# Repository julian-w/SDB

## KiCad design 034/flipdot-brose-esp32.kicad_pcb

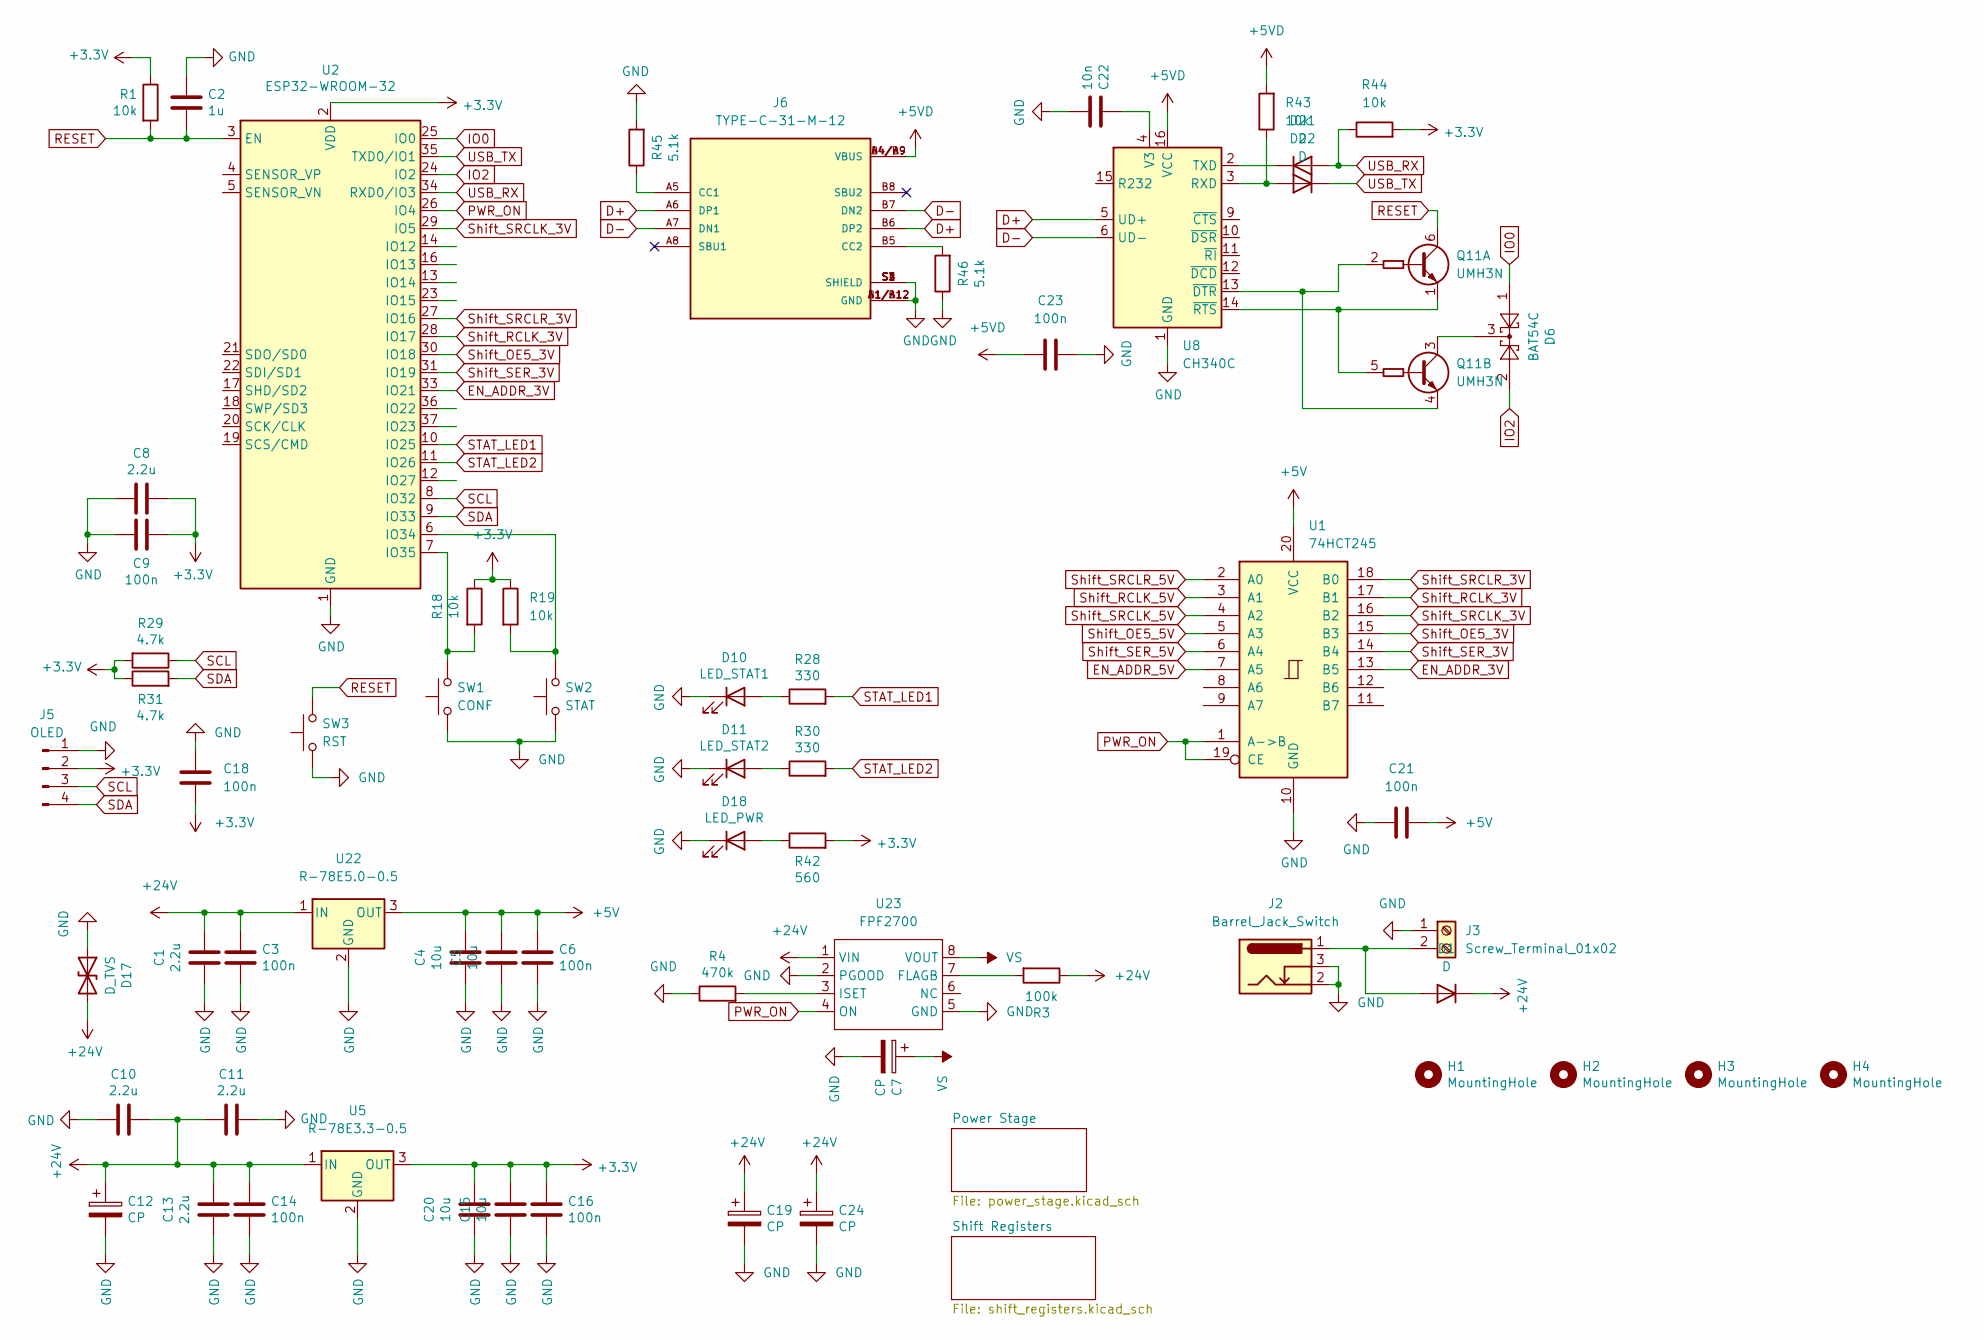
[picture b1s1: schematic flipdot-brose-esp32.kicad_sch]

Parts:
C1, C10, C11, C13: 2.2u; C_0805_2012Metric; LCSC C49217
C2: 1u; C_0603_1608Metric; LCSC C15849
C3, C14: 100n; C_0805_2012Metric; LCSC C49678
C4, C5, C15, C20: 10u; C_0805_2012Metric; LCSC C440198
C6, C9, C16, C18, C21, C23: 100n; C_0603_1608Metric; LCSC C14663
C7, C12, C19, C24: CP; C_Elec_6.3x7.7; LCSC C176683
C8: 2.2u; C_0603_1608Metric; LCSC C23630
C22: 10n; C_0603_1608Metric; LCSC C57112
D1: D; D_SMA; LCSC C14996
D6: BAT54C; SOT-23; LCSC C37704
D10: LED_STAT1; LED_0603_1608Metric; LCSC C72041
D11: LED_STAT2; LED_0603_1608Metric; LCSC C2290
D17: D_TVS; D_SMA; LCSC C152118
D18: LED_PWR; LED_0603_1608Metric; LCSC C2286
D21, D22: D; D_SOD-123; LCSC C81598
H1, H2, H3, H4: MountingHole; MountingHole_2.7mm_M2.5
J2: Barrel_Jack_Switch; BarrelJack_Horizontal
J3: Screw_Terminal_01x02; PhoenixContact_MCV_1,5_2-G-3.5_1x02_P3.50mm_Vertical
J5: OLED; SSD1306-0.91-OLED-4pin-128x32
J6: TYPE-C-31-M-12; HRO_TYPE-C-31-M-12; PARTREV 2020.12.08; LCSC C165948
Q11: UMH3N; SOT-363_SC-70-6; LCSC C62892
R1, R18, R19, R43, R44: 10k; R_0603_1608Metric; LCSC C25804
R3: 100k; R_0603_1608Metric; LCSC C25803
R4: 470k; R_0603_1608Metric; LCSC C23178
R28, R30: 330; R_0603_1608Metric; LCSC C23138
R29, R31: 4.7k; R_0603_1608Metric; LCSC C23162
R42: 560; R_0603_1608Metric; LCSC C23204
R45, R46: 5.1k; R_0603_1608Metric; LCSC C23186
SW1: CONF; SW_Push_1P1T_NO_6x6mm_H9.5mm; LCSC C2837532
SW2: STAT; SW_Push_1P1T_NO_6x6mm_H9.5mm; LCSC C2837532
SW3: RST; SW_Push_1P1T_NO_6x6mm_H9.5mm; LCSC C2837532
U1: 74HCT245; TSSOP-20_4.4x6.5mm_P0.65mm; LCSC C5980
U2: ESP32-WROOM-32; ESP32-WROOM-32U; LCSC C529579
U5: R-78E3.3-0.5; Converter_DCDC_RECOM_R-78E-0.5_THT
U8: CH340C; SOIC-16_3.9x9.9mm_P1.27mm; LCSC C84681
U22: R-78E5.0-0.5; Converter_DCDC_RECOM_R-78E-0.5_THT
U23: FPF2700; SOP-8_3.9x4.9mm_P1.27mm

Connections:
+3V3: C8.1, C9.1, C15.1, C16.1, C18.2, C20.1, J5.2, R1.1, R18.1, R19.1, R29.2, R31.1, R42.2, R44.2, U2.2 (VDD), U5.3 (OUT)
+5V: C4.1, C5.1, C6.1, C21.2, U1.20 (VCC), U22.3 (OUT); also elsewhere on the board
+5VD: C23.2, J6.A4/B9 (VBUS), J6.B4/A9 (VBUS), R43.2, U8.16 (VCC)
+24V: C1.1, C3.1, C10.1, C11.1, C12.1, C13.1, C14.1, C19.1, C24.1, D1.1 (K), D17.2 (A2), R3.1, U5.1 (IN), U22.1 (IN), U23.1 (VIN); also elsewhere on the board
D+: J6.A6 (DP1), J6.B6 (DP2), U8.5 (UD+)
D-: J6.A7 (DN1), J6.B7 (DN2), U8.6 (UD-)
EN_ADDR_3V: U1.13 (B5), U2.33 (IO21)
EN_ADDR_5V: U1.7 (A5); also elsewhere on the board
GND: C1.2, C2.2, C3.2, C4.2, C5.2, C6.2, C7.2, C8.2, C9.2, C10.2, C11.2, C12.2, C13.2, C14.2, C15.2, C16.2, C18.1, C19.2, C20.2, C21.1, C22.2, C23.1, C24.2, D10.1 (K), D11.1 (K), D17.1 (A1), D18.1 (K), J2.2, J2.3, J3.1, J5.1, J6.A1/B12 (GND), J6.B1/A12 (GND), J6.S1 (SHIELD), J6.S2 (SHIELD), J6.S3 (SHIELD), J6.S4 (SHIELD), R4.1, R45.2, R46.1, SW1.1, SW2.1, SW3.1, U1.10 (GND), U2.1 (GND), U2.15 (GND), U2.38 (GND), U2.39 (GND), U5.2 (GND), U8.1 (GND), U22.2 (GND), U23.2 (PGOOD), U23.5 (GND); also elsewhere on the board
IO0: D6.1, U2.25 (IO0)
IO2: D6.2, U2.24 (IO2)
unnamed: C22.1, U8.4 (V3)
unnamed: D1.2 (A), J2.1, J3.2
unnamed: D6.3, Q11.3 (C2)
unnamed: D10.2 (A), R28.1
unnamed: D11.2 (A), R30.1
unnamed: D18.2 (A), R42.1
unnamed: D21.1 (K), U8.2 (TXD)
unnamed: D22.2 (A), R43.1, U8.3 (RXD)
unnamed: J6.A5 (CC1), R45.1
unnamed: J6.B5 (CC2), R46.2
unnamed: Q11.1 (E1), Q11.5 (B2), U8.14 (~RTS)
unnamed: Q11.2 (B1), Q11.4 (E2), U8.13 (~DTR)
unnamed: R3.2, U23.7 (FLAGB)
unnamed: R4.2, U23.3 (ISET)
unnamed: R18.2, SW1.2, U2.7 (IO35)
unnamed: R19.2, SW2.2, U2.6 (IO34)
PWR_ON: U1.1 (A->B), U1.19 (CE), U2.26 (IO4), U23.4 (ON)
RESET: C2.1, Q11.6 (C1), R1.2, SW3.2, U2.3 (EN)
SCL: J5.3, R29.1, U2.8 (IO32)
SDA: J5.4, R31.2, U2.9 (IO33)
STAT_LED1: R28.2, U2.10 (IO25)
STAT_LED2: R30.2, U2.11 (IO26)
Shift_OE5_3V: U1.15 (B3), U2.30 (IO18)
Shift_OE5_5V: U1.5 (A3); also elsewhere on the board
Shift_RCLK_3V: U1.17 (B1), U2.28 (IO17)
Shift_RCLK_5V: U1.3 (A1); also elsewhere on the board
Shift_SER_3V: U1.14 (B4), U2.31 (IO19)
Shift_SER_5V: U1.6 (A4); also elsewhere on the board
Shift_SRCLK_3V: U1.16 (B2), U2.29 (IO5)
Shift_SRCLK_5V: U1.4 (A2); also elsewhere on the board
Shift_SRCLR_3V: U1.18 (B0), U2.27 (IO16)
Shift_SRCLR_5V: U1.2 (A0); also elsewhere on the board
USB_RX: D21.2 (A), R44.1, U2.34 (RXD0/IO3)
USB_TX: D22.1 (K), U2.35 (TXD0/IO1)
VS: C7.1, U23.8 (VOUT); also elsewhere on the board

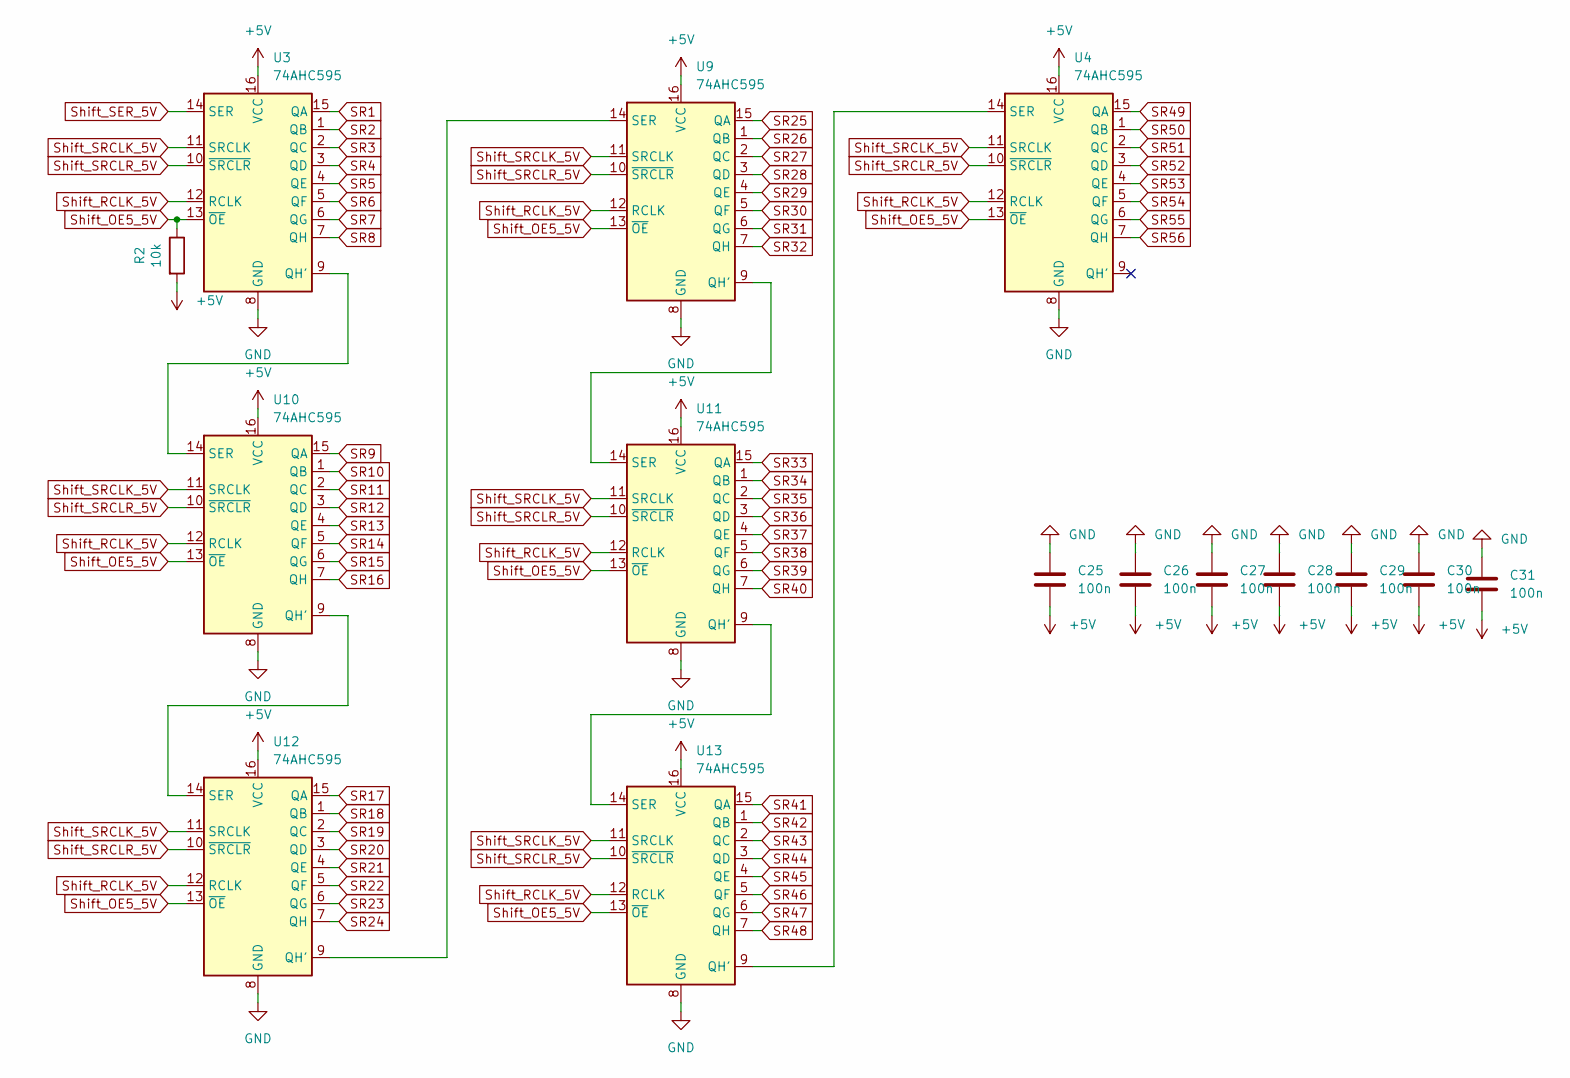
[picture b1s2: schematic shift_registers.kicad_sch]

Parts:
C25, C26, C27, C28, C29, C30, C31: 100n; C_0603_1608Metric; LCSC C14663
R2: 10k; R_0603_1608Metric; LCSC C25804
U3, U4, U9, U10, U11, U12, U13: 74AHC595; TSSOP-16_4.4x5mm_P0.65mm; LCSC C271269

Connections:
+5V: C25.2, C26.2, C27.2, C28.2, C29.2, C30.2, C31.2, R2.2, U3.16 (VCC), U4.16 (VCC), U9.16 (VCC), U10.16 (VCC), U11.16 (VCC), U12.16 (VCC), U13.16 (VCC); also elsewhere on the board
GND: C25.1, C26.1, C27.1, C28.1, C29.1, C30.1, C31.1, U3.8 (GND), U4.8 (GND), U9.8 (GND), U10.8 (GND), U11.8 (GND), U12.8 (GND), U13.8 (GND); also elsewhere on the board
unnamed: U10.9 (QH'), U12.14 (SER)
unnamed: U3.9 (QH'), U10.14 (SER)
unnamed: U11.9 (QH'), U13.14 (SER)
unnamed: U9.9 (QH'), U11.14 (SER)
unnamed: U9.14 (SER), U12.9 (QH')
unnamed: U4.14 (SER), U13.9 (QH')
SR1: U3.15 (QA); also elsewhere on the board
SR2: U3.1 (QB); also elsewhere on the board
SR3: U3.2 (QC); also elsewhere on the board
SR4: U3.3 (QD); also elsewhere on the board
SR5: U3.4 (QE); also elsewhere on the board
SR6: U3.5 (QF); also elsewhere on the board
SR7: U3.6 (QG); also elsewhere on the board
SR8: U3.7 (QH); also elsewhere on the board
SR9: U10.15 (QA); also elsewhere on the board
SR10: U10.1 (QB); also elsewhere on the board
SR11: U10.2 (QC); also elsewhere on the board
SR12: U10.3 (QD); also elsewhere on the board
SR13: U10.4 (QE); also elsewhere on the board
SR14: U10.5 (QF); also elsewhere on the board
SR15: U10.6 (QG); also elsewhere on the board
SR16: U10.7 (QH); also elsewhere on the board
SR17: U12.15 (QA); also elsewhere on the board
SR18: U12.1 (QB); also elsewhere on the board
SR19: U12.2 (QC); also elsewhere on the board
SR20: U12.3 (QD); also elsewhere on the board
SR21: U12.4 (QE); also elsewhere on the board
SR22: U12.5 (QF); also elsewhere on the board
SR23: U12.6 (QG); also elsewhere on the board
SR24: U12.7 (QH); also elsewhere on the board
SR25: U9.15 (QA); also elsewhere on the board
SR26: U9.1 (QB); also elsewhere on the board
SR27: U9.2 (QC); also elsewhere on the board
SR28: U9.3 (QD); also elsewhere on the board
SR29: U9.4 (QE); also elsewhere on the board
SR30: U9.5 (QF); also elsewhere on the board
SR31: U9.6 (QG); also elsewhere on the board
SR32: U9.7 (QH); also elsewhere on the board
SR33: U11.15 (QA); also elsewhere on the board
SR34: U11.1 (QB); also elsewhere on the board
SR35: U11.2 (QC); also elsewhere on the board
SR36: U11.3 (QD); also elsewhere on the board
SR37: U11.4 (QE); also elsewhere on the board
SR38: U11.5 (QF); also elsewhere on the board
SR39: U11.6 (QG); also elsewhere on the board
SR40: U11.7 (QH); also elsewhere on the board
SR41: U13.15 (QA); also elsewhere on the board
SR42: U13.1 (QB); also elsewhere on the board
SR43: U13.2 (QC); also elsewhere on the board
SR44: U13.3 (QD); also elsewhere on the board
SR45: U13.4 (QE); also elsewhere on the board
SR46: U13.5 (QF); also elsewhere on the board
SR47: U13.6 (QG); also elsewhere on the board
SR48: U13.7 (QH); also elsewhere on the board
SR49: U4.15 (QA); also elsewhere on the board
SR50: U4.1 (QB); also elsewhere on the board
SR51: U4.2 (QC); also elsewhere on the board
SR52: U4.3 (QD); also elsewhere on the board
SR53: U4.4 (QE); also elsewhere on the board
SR54: U4.5 (QF)
SR55: U4.6 (QG)
SR56: U4.7 (QH)
Shift_OE5_5V: R2.1, U3.13 (~OE), U4.13 (~OE), U9.13 (~OE), U10.13 (~OE), U11.13 (~OE), U12.13 (~OE), U13.13 (~OE); also elsewhere on the board
Shift_RCLK_5V: U3.12 (RCLK), U4.12 (RCLK), U9.12 (RCLK), U10.12 (RCLK), U11.12 (RCLK), U12.12 (RCLK), U13.12 (RCLK); also elsewhere on the board
Shift_SER_5V: U3.14 (SER); also elsewhere on the board
Shift_SRCLK_5V: U3.11 (SRCLK), U4.11 (SRCLK), U9.11 (SRCLK), U10.11 (SRCLK), U11.11 (SRCLK), U12.11 (SRCLK), U13.11 (SRCLK); also elsewhere on the board
Shift_SRCLR_5V: U3.10 (~SRCLR), U4.10 (~SRCLR), U9.10 (~SRCLR), U10.10 (~SRCLR), U11.10 (~SRCLR), U12.10 (~SRCLR), U13.10 (~SRCLR); also elsewhere on the board

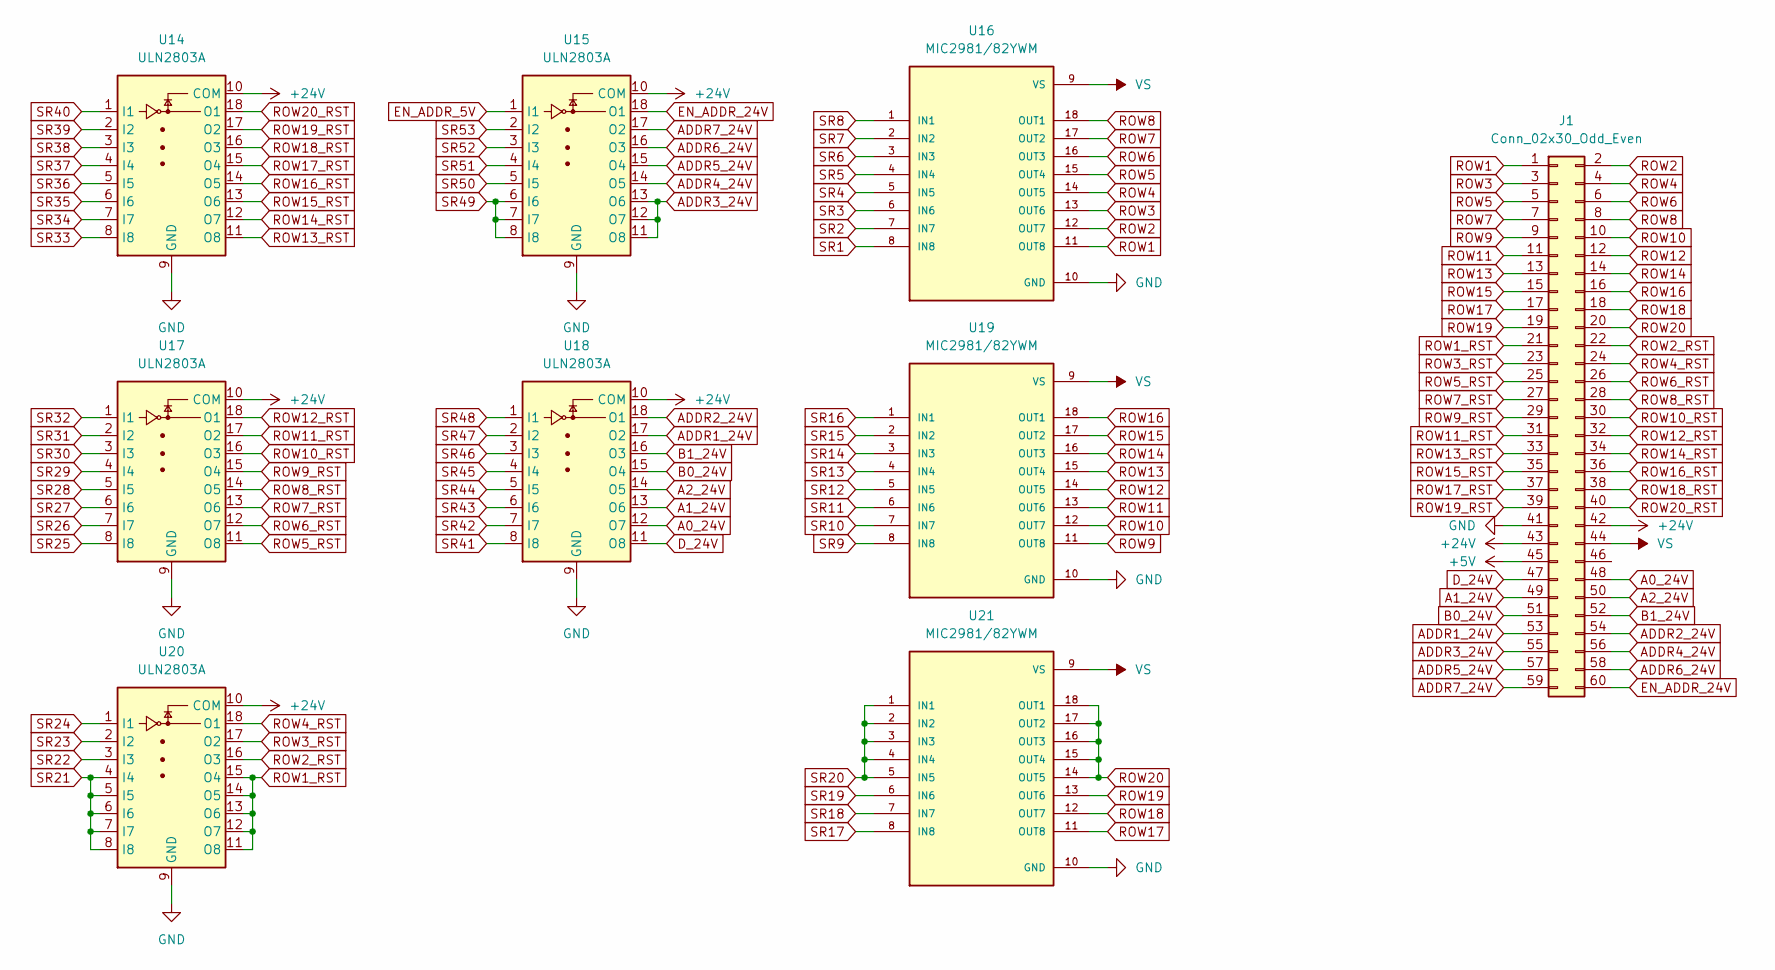
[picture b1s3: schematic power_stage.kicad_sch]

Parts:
J1: Conn_02x30_Odd_Even; IDC-Header_2x30-1MP_P2.54mm_Latch_Vertical
U14, U15, U17, U18, U20: ULN2803A; SOIC-18W_7.5x11.6mm_P1.27mm; LCSC C845537
U16, U19, U21: MIC2981/82YWM; SOP-18_7x12.5mm_P1.27mm; PARTREV June 2005

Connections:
+5V: J1.45; also elsewhere on the board
+24V: J1.42, J1.43, U14.10 (COM), U15.10 (COM), U17.10 (COM), U18.10 (COM), U20.10 (COM); also elsewhere on the board
A0_24V: J1.48, U18.12 (O7)
A1_24V: J1.49, U18.13 (O6)
A2_24V: J1.50, U18.14 (O5)
ADDR1_24V: J1.53, U18.17 (O2)
ADDR2_24V: J1.54, U18.18 (O1)
ADDR3_24V: J1.55, U15.11 (O8), U15.12 (O7), U15.13 (O6)
ADDR4_24V: J1.56, U15.14 (O5)
ADDR5_24V: J1.57, U15.15 (O4)
ADDR6_24V: J1.58, U15.16 (O3)
ADDR7_24V: J1.59, U15.17 (O2)
B0_24V: J1.51, U18.15 (O4)
B1_24V: J1.52, U18.16 (O3)
D_24V: J1.47, U18.11 (O8)
EN_ADDR_5V: U15.1 (I1); also elsewhere on the board
EN_ADDR_24V: J1.60, U15.18 (O1)
GND: J1.41, U14.9 (GND), U15.9 (GND), U16.10 (GND), U17.9 (GND), U18.9 (GND), U19.10 (GND), U20.9 (GND), U21.10 (GND); also elsewhere on the board
ROW1: J1.1, U16.11 (OUT8)
ROW1_RST: J1.21, U20.11 (O8), U20.12 (O7), U20.13 (O6), U20.14 (O5), U20.15 (O4)
ROW2: J1.2, U16.12 (OUT7)
ROW2_RST: J1.22, U20.16 (O3)
ROW3: J1.3, U16.13 (OUT6)
ROW3_RST: J1.23, U20.17 (O2)
ROW4: J1.4, U16.14 (OUT5)
ROW4_RST: J1.24, U20.18 (O1)
ROW5: J1.5, U16.15 (OUT4)
ROW5_RST: J1.25, U17.11 (O8)
ROW6: J1.6, U16.16 (OUT3)
ROW6_RST: J1.26, U17.12 (O7)
ROW7: J1.7, U16.17 (OUT2)
ROW7_RST: J1.27, U17.13 (O6)
ROW8: J1.8, U16.18 (OUT1)
ROW8_RST: J1.28, U17.14 (O5)
ROW9: J1.9, U19.11 (OUT8)
ROW9_RST: J1.29, U17.15 (O4)
ROW10: J1.10, U19.12 (OUT7)
ROW10_RST: J1.30, U17.16 (O3)
ROW11: J1.11, U19.13 (OUT6)
ROW11_RST: J1.31, U17.17 (O2)
ROW12: J1.12, U19.14 (OUT5)
ROW12_RST: J1.32, U17.18 (O1)
ROW13: J1.13, U19.15 (OUT4)
ROW13_RST: J1.33, U14.11 (O8)
ROW14: J1.14, U19.16 (OUT3)
ROW14_RST: J1.34, U14.12 (O7)
ROW15: J1.15, U19.17 (OUT2)
ROW15_RST: J1.35, U14.13 (O6)
ROW16: J1.16, U19.18 (OUT1)
ROW16_RST: J1.36, U14.14 (O5)
ROW17: J1.17, U21.11 (OUT8)
ROW17_RST: J1.37, U14.15 (O4)
ROW18: J1.18, U21.12 (OUT7)
ROW18_RST: J1.38, U14.16 (O3)
ROW19: J1.19, U21.13 (OUT6)
ROW19_RST: J1.39, U14.17 (O2)
ROW20: J1.20, U21.14 (OUT5), U21.15 (OUT4), U21.16 (OUT3), U21.17 (OUT2), U21.18 (OUT1)
ROW20_RST: J1.40, U14.18 (O1)
SR1: U16.8 (IN8); also elsewhere on the board
SR2: U16.7 (IN7); also elsewhere on the board
SR3: U16.6 (IN6); also elsewhere on the board
SR4: U16.5 (IN5); also elsewhere on the board
SR5: U16.4 (IN4); also elsewhere on the board
SR6: U16.3 (IN3); also elsewhere on the board
SR7: U16.2 (IN2); also elsewhere on the board
SR8: U16.1 (IN1); also elsewhere on the board
SR9: U19.8 (IN8); also elsewhere on the board
SR10: U19.7 (IN7); also elsewhere on the board
SR11: U19.6 (IN6); also elsewhere on the board
SR12: U19.5 (IN5); also elsewhere on the board
SR13: U19.4 (IN4); also elsewhere on the board
SR14: U19.3 (IN3); also elsewhere on the board
SR15: U19.2 (IN2); also elsewhere on the board
SR16: U19.1 (IN1); also elsewhere on the board
SR17: U21.8 (IN8); also elsewhere on the board
SR18: U21.7 (IN7); also elsewhere on the board
SR19: U21.6 (IN6); also elsewhere on the board
SR20: U21.1 (IN1), U21.2 (IN2), U21.3 (IN3), U21.4 (IN4), U21.5 (IN5); also elsewhere on the board
SR21: U20.4 (I4), U20.5 (I5), U20.6 (I6), U20.7 (I7), U20.8 (I8); also elsewhere on the board
SR22: U20.3 (I3); also elsewhere on the board
SR23: U20.2 (I2); also elsewhere on the board
SR24: U20.1 (I1); also elsewhere on the board
SR25: U17.8 (I8); also elsewhere on the board
SR26: U17.7 (I7); also elsewhere on the board
SR27: U17.6 (I6); also elsewhere on the board
SR28: U17.5 (I5); also elsewhere on the board
SR29: U17.4 (I4); also elsewhere on the board
SR30: U17.3 (I3); also elsewhere on the board
SR31: U17.2 (I2); also elsewhere on the board
SR32: U17.1 (I1); also elsewhere on the board
SR33: U14.8 (I8); also elsewhere on the board
SR34: U14.7 (I7); also elsewhere on the board
SR35: U14.6 (I6); also elsewhere on the board
SR36: U14.5 (I5); also elsewhere on the board
SR37: U14.4 (I4); also elsewhere on the board
SR38: U14.3 (I3); also elsewhere on the board
SR39: U14.2 (I2); also elsewhere on the board
SR40: U14.1 (I1); also elsewhere on the board
SR41: U18.8 (I8); also elsewhere on the board
SR42: U18.7 (I7); also elsewhere on the board
SR43: U18.6 (I6); also elsewhere on the board
SR44: U18.5 (I5); also elsewhere on the board
SR45: U18.4 (I4); also elsewhere on the board
SR46: U18.3 (I3); also elsewhere on the board
SR47: U18.2 (I2); also elsewhere on the board
SR48: U18.1 (I1); also elsewhere on the board
SR49: U15.6 (I6), U15.7 (I7), U15.8 (I8); also elsewhere on the board
SR50: U15.5 (I5); also elsewhere on the board
SR51: U15.4 (I4); also elsewhere on the board
SR52: U15.3 (I3); also elsewhere on the board
SR53: U15.2 (I2); also elsewhere on the board
VS: J1.44, U16.9 (VS), U19.9 (VS), U21.9 (VS); also elsewhere on the board

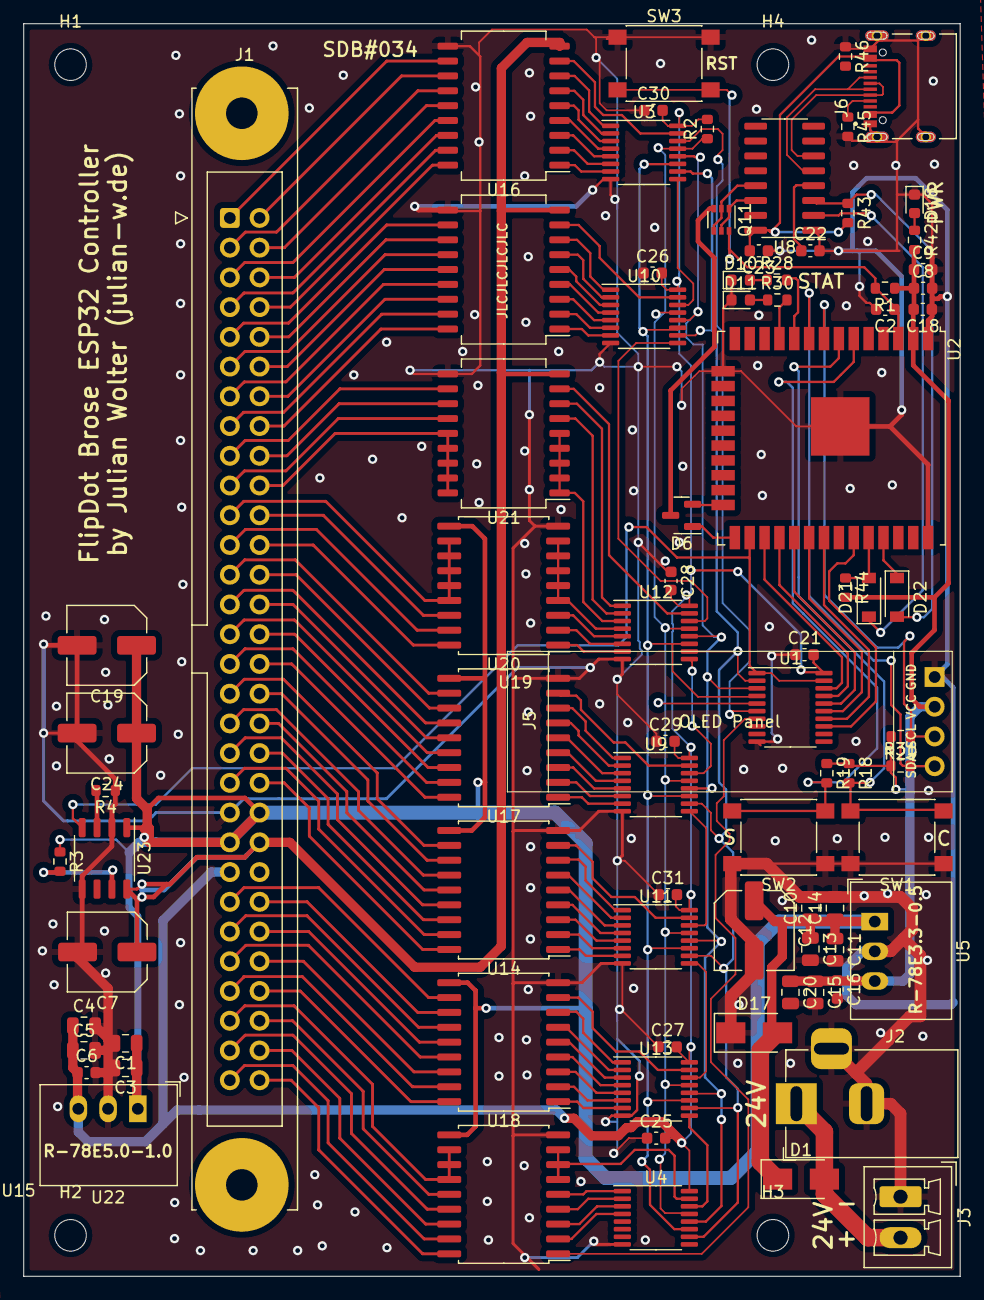
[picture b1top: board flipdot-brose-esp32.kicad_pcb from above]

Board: 2 copper layers, 80.0 x 107.0 mm, 87 parts (0 on the bottom side), 159 nets.

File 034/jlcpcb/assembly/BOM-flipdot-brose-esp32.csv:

Comment,Designator,Footprint,LCSC
100n,"C16,C18,C21,C23,C25,C26,C27,C28,C29,C30,C31,C6,C9",C_0603_1608Metric,C14663
D,D1,D_SMA,C14996
D_TVS,D17,D_SMA,C152118
1u,C2,C_0603_1608Metric,C15849
TYPE-C-31-M-12,J6,HRO_TYPE-C-31-M-12,C165948
CP,"C12,C19,C24,C7",C_Elec_6.3x7.7,C176683
LED_PWR,D18,LED_0603_1608Metric,C2286
LED_STAT2,D11,LED_0603_1608Metric,C2290
330,"R28,R30",R_0603_1608Metric,C23138
4.7k,"R29,R31",R_0603_1608Metric,C23162
470k,R4,R_0603_1608Metric,C23178
5.1k,"R45,R46",R_0603_1608Metric,C23186
560,R42,R_0603_1608Metric,C23204
2.2u,C8,C_0603_1608Metric,C23630
100k,R3,R_0603_1608Metric,C25803
10k,"R1,R18,R19,R2,R43,R44",R_0603_1608Metric,C25804
74AHC595,"U10,U11,U12,U13,U3,U4,U9",TSSOP-16_4.4x5mm_P0.65mm,C271269
CONF,"SW1,SW2,SW3",SW_Push_1P1T_NO_6x6mm_H9.5mm,C2837532
BAT54C,D6,SOT-23,C37704
10u,"C15,C20,C4,C5",C_0805_2012Metric,C440198
2.2u,"C1,C10,C11,C13",C_0805_2012Metric,C49217
100n,"C14,C3",C_0805_2012Metric,C49678
ESP32-WROOM-32,U2,ESP32-WROOM-32U,C529579
10n,C22,C_0603_1608Metric,C57112
74HCT245,U1,TSSOP-20_4.4x6.5mm_P0.65mm,C5980
UMH3N,Q11,SOT-363_SC-70-6,C62892
LED_STAT1,D10,LED_0603_1608Metric,C72041
D,"D21,D22",D_SOD-123,C81598
ULN2803A,"U14,U15,U17,U18,U20",SOIC-18W_7.5x11.6mm_P1.27mm,C845537
CH340C,U8,SOIC-16_3.9x9.9mm_P1.27mm,C84681
R-78E3.3-0.5,U5,Converter_DCDC_RECOM_R-78E-0.5_THT,
OLED,J5,SSD1306-0.91-OLED-4pin-128x32,
MountingHole,H4,MountingHole_2.7mm_M2.5,
MountingHole,H3,MountingHole_2.7mm_M2.5,
MountingHole,H2,MountingHole_2.7mm_M2.5,
MountingHole,H1,MountingHole_2.7mm_M2.5,
Barrel_Jack_Switch,J2,BarrelJack_Horizontal,
Screw_Terminal_01x02,J3,"PhoenixContact_MCV_1,5_2-G-3.5_1x02_P3.50mm_Vertical",
Conn_02x30_Odd_Even,J1,IDC-Header_2x30-1MP_P2.54mm_Latch_Vertical,
FPF2700,U23,SOP-8_3.9x4.9mm_P1.27mm,
R-78E5.0-0.5,U22,Converter_DCDC_RECOM_R-78E-0.5_THT,
MIC2981/82YWM,U21,SOP-18_7x12.5mm_P1.27mm,
MIC2981/82YWM,U19,SOP-18_7x12.5mm_P1.27mm,
MIC2981/82YWM,U16,SOP-18_7x12.5mm_P1.27mm,

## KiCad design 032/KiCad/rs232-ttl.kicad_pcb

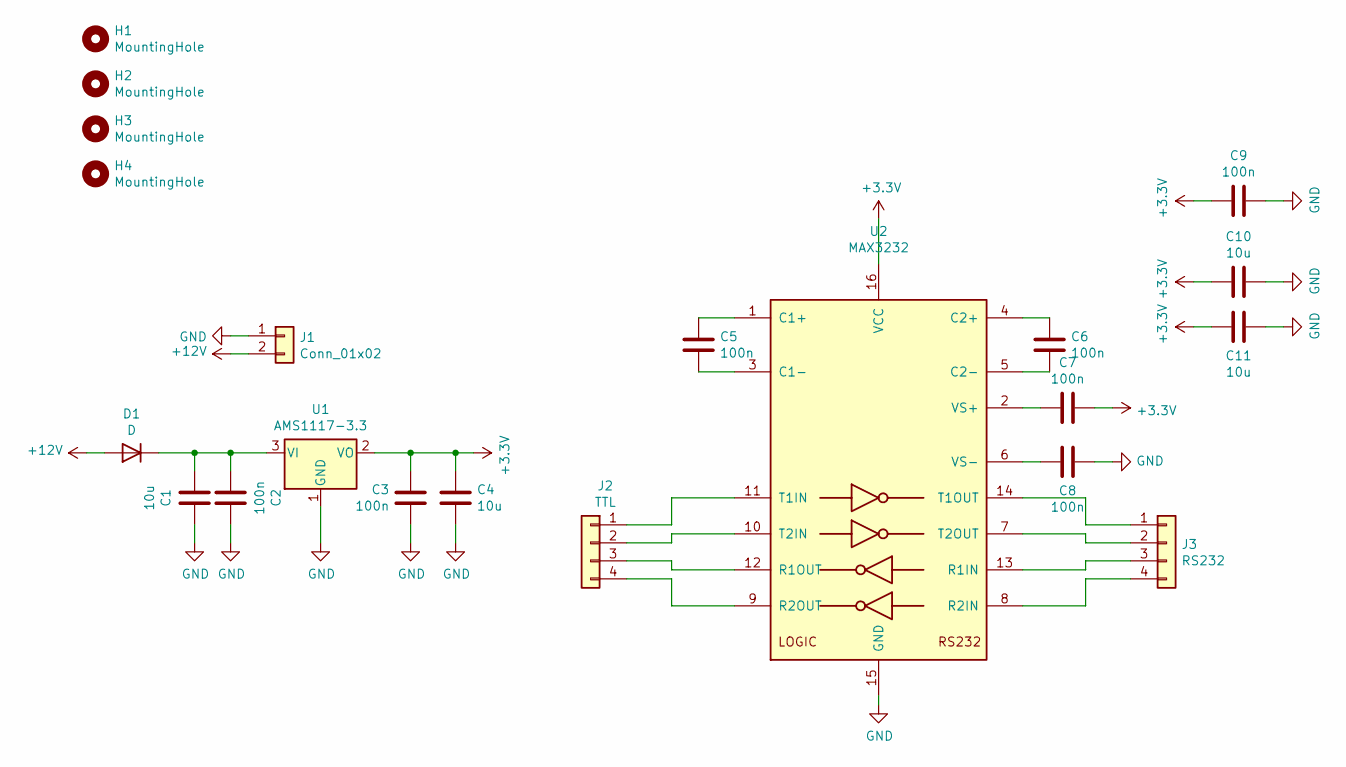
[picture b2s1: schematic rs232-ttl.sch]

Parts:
C1: 10u; C_1206
C2, C3, C5, C6, C7, C8, C9: 100n; C_0603
C4, C10, C11: 10u; C_0805
D1: D; D_SOD-123F
H1, H2, H3, H4: MountingHole; MountingHole_3.2mm_M3
J1: Conn_01x02; PinHeader_1x02_P2.54mm_Vertical
J2: TTL; PinHeader_1x04_P2.54mm_Vertical
J3: RS232; PinHeader_1x04_P2.54mm_Vertical
U1: AMS1117-3.3; SOT-223-3_TabPin2
U2: MAX3232; SSOP-16_4.4x5.2mm_Pitch0.65mm

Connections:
+3V3: C3.1, C4.1, C7.1, C9.1, C10.1, C11.1, U1.2 (VO), U2.16 (VCC)
+12V: D1.2 (A), J1.2
GND: C1.2, C2.2, C3.2, C4.2, C8.1, C9.2, C10.2, C11.2, J1.1, U1.1 (GND), U2.15 (GND)
unnamed: C1.1, C2.1, D1.1 (K), U1.3 (VI)
unnamed: C5.1, U2.3 (C1-)
unnamed: C5.2, U2.1 (C1+)
unnamed: C6.1, U2.5 (C2-)
unnamed: C6.2, U2.4 (C2+)
unnamed: C7.2, U2.2 (VS+)
unnamed: C8.2, U2.6 (VS-)
unnamed: J2.1, U2.11 (T1IN)
unnamed: J2.2, U2.10 (T2IN)
unnamed: J2.3, U2.12 (R1OUT)
unnamed: J2.4, U2.9 (R2OUT)
unnamed: J3.1, U2.14 (T1OUT)
unnamed: J3.2, U2.7 (T2OUT)
unnamed: J3.3, U2.13 (R1IN)
unnamed: J3.4, U2.8 (R2IN)

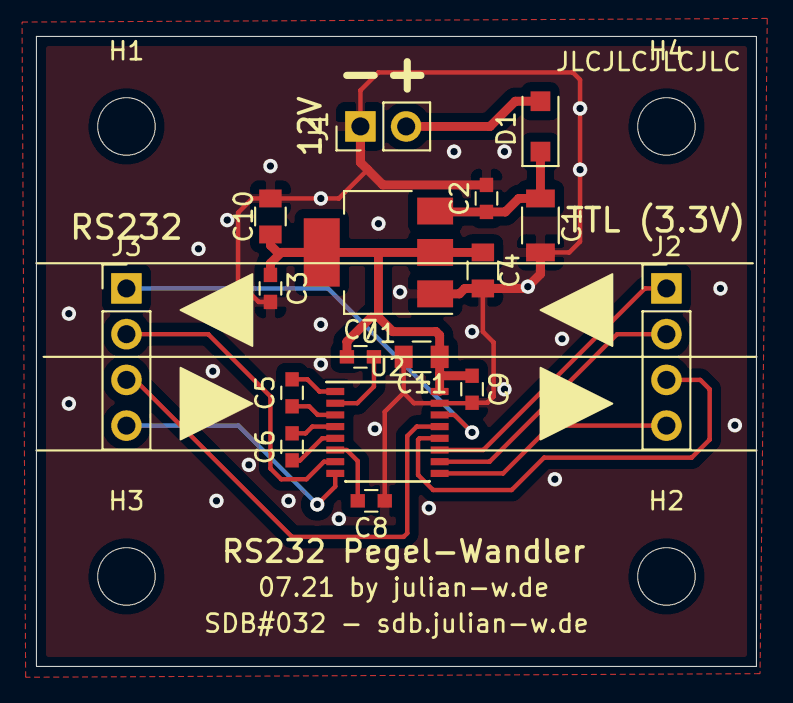
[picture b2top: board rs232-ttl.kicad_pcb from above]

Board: 2 copper layers, 40.0 x 35.0 mm, 21 parts (0 on the bottom side), 18 nets.

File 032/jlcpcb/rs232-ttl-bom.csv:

Comment,Designator,Footprint,LCSC
10u,C1,Capacitors_SMD:C_1206,C13585
10u,"C4,C10,C11",Capacitors_SMD:C_0805,C15850
100n,"C2,C3,C5,C6,C7,C8,C9",Capacitors_SMD:C_0603,C14663
D,D1,Diodes_SMD:D_SOD-123F,C64898
MountingHole,"H1,H2,H3,H4",Mounting_Holes:MountingHole_3.2mm_M3,
Conn_01x02,J1,Connector_PinHeader_2.54mm:PinHeader_1x02_P2.54mm_Vertical,
TTL,J2,Connector_PinHeader_2.54mm:PinHeader_1x04_P2.54mm_Vertical,
RS232,J3,Connector_PinHeader_2.54mm:PinHeader_1x04_P2.54mm_Vertical,
AMS1117-3.3,U1,Package_TO_SOT_SMD:SOT-223-3_TabPin2,C6186
MAX3232,U2,Housings_SSOP:SSOP-16_4.4x5.2mm_Pitch0.65mm,C9951
